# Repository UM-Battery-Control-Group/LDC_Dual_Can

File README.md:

# LDCquadCan
 can based LDC sensor

 Forgot to tie boot0 to ground so need to set nboot option in cube programmer

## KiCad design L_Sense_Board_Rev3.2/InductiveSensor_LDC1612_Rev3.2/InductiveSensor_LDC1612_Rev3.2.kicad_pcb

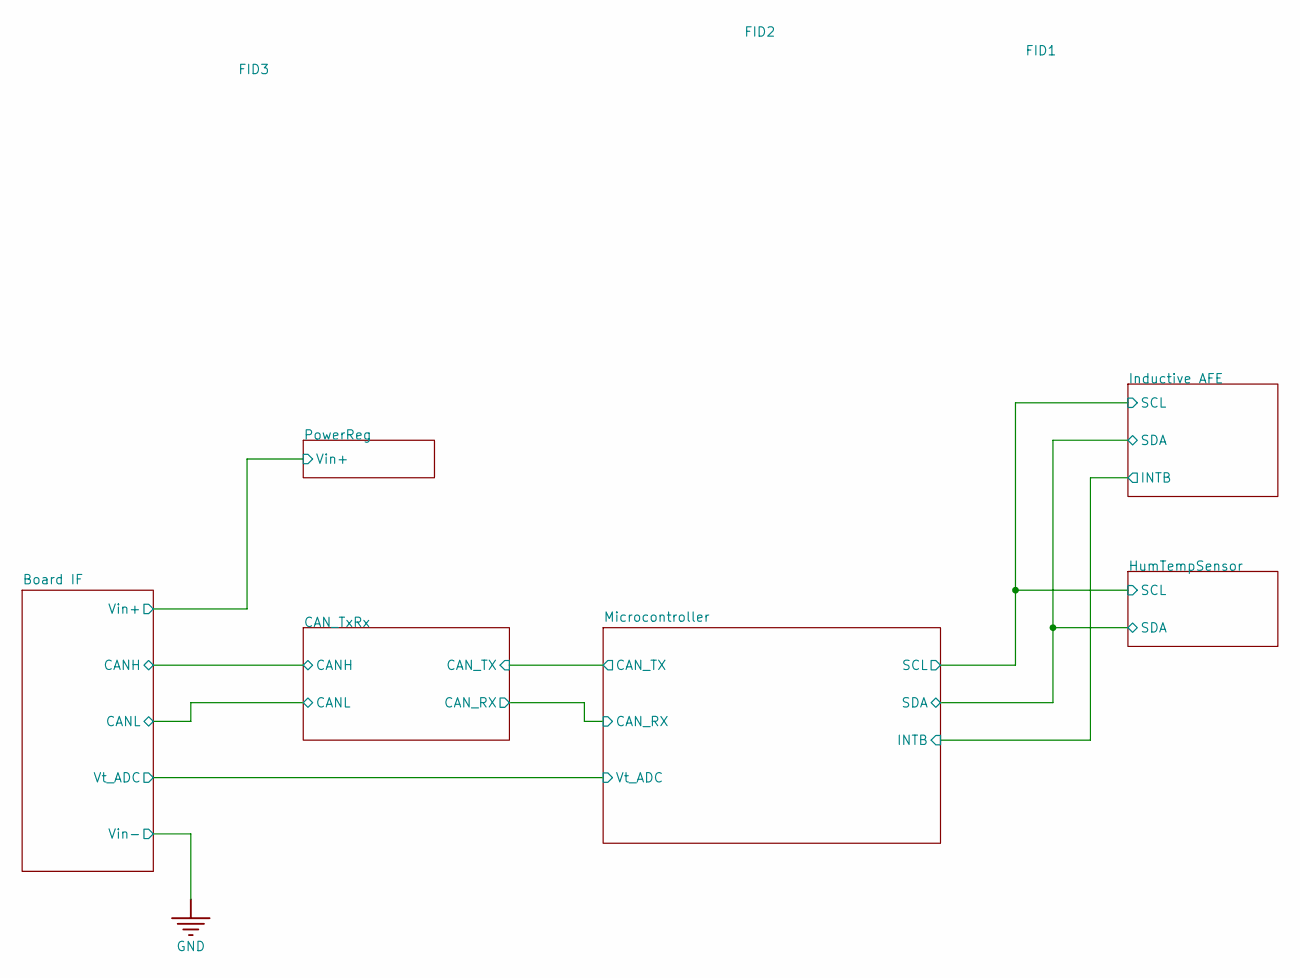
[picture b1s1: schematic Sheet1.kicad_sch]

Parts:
FID1, FID2, FID3: Fiducial; FID

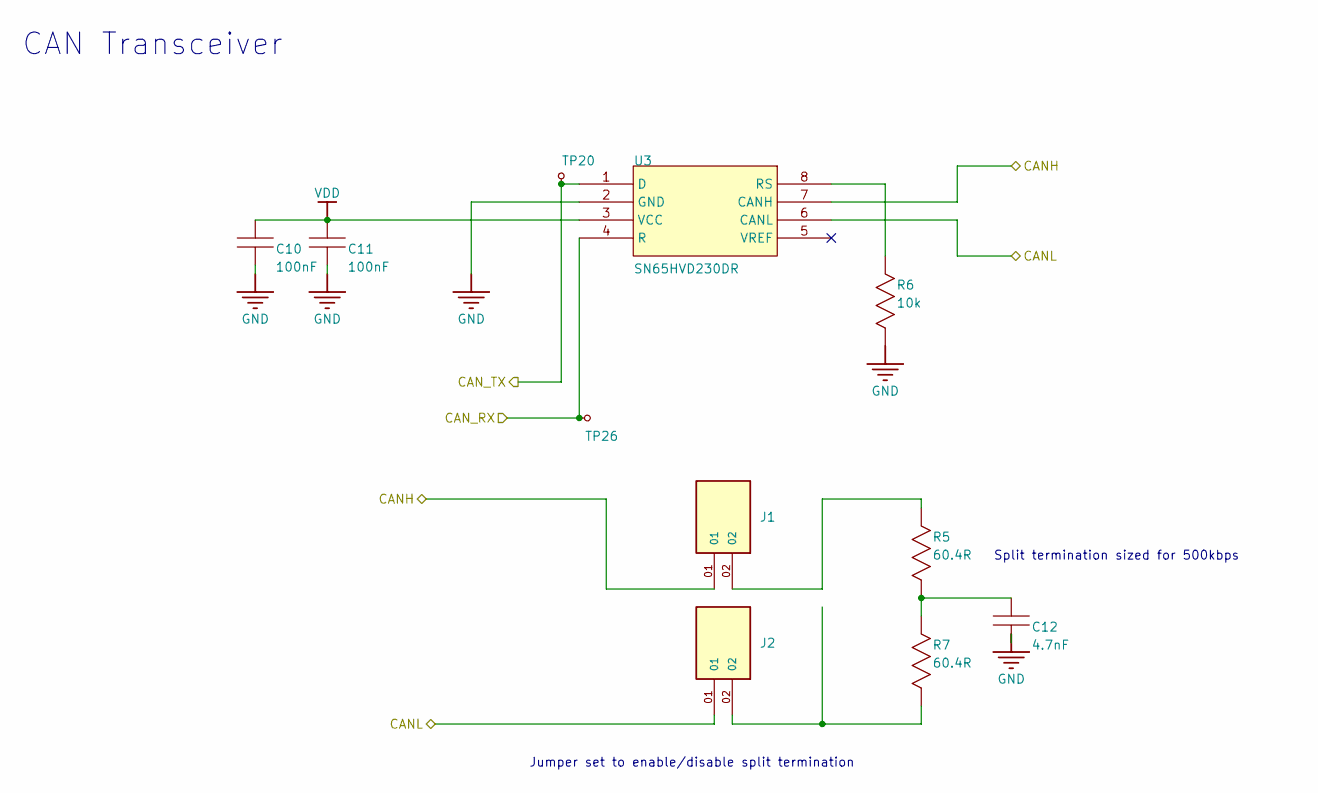
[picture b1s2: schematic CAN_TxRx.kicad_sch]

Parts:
C10, C11: 100nF; CAP0805; TOLERANCE 10%; VOLTAGE 50V; MANUFACTURER PART NUMBER CC0805KRX7R9BB104; LCSC PART# C49678
C12: 4.7nF; C0603; MANUFACTURER PART NUMBER C0603C472K1TACAUTO; LCSC PART# C3882427
J1, J2: TSM-102-01-X-SV; SAMTEC_TSM-102-01-X-SV; PARTREV D; DigiKey_Part_Number 612-TSM-102-01-S-SV-P-TRCT-ND
R5, R7: 60.4R; R0603; POWER RATING 100mW; TOLERANCE 1%; MANUFACTURER PART NUMBER RC0603FR-0760R4L; LCSC PART# C245987
R6: 10k; R0603; TOLERANCE 1%; VOLTAGE RATING (AC) 50V; MANUFACTURER PART NUMBER RC0603FR-0710KL; LCSC PART# C98220
TP20, TP26: 1mm Test Point; TP_1MM
U3: SN65HVD230DR; SOIC_8; MANUFACTURER PART NUMBER SN65HVD230DR; LCSC PART# C12084

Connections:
//Board IF/CANH: J1.01, U3.7 (CANH); also elsewhere on the board
//Board IF/CANL: J2.01, U3.6 (CANL); also elsewhere on the board
//CAN_TxRx/CAN_RX: TP26.1 (0), U3.4 (R); also elsewhere on the board
//CAN_TxRx/CAN_TX: TP20.1 (0), U3.1 (D); also elsewhere on the board
GND: C10.2, C11.2, C12.2, R6.2, U3.2 (GND); also elsewhere on the board
unnamed: C12.1, R5.2, R7.1
unnamed: J1.02, R5.1
unnamed: J2.02, R7.2
unnamed: R6.1, U3.8 (RS)
VDD: C10.1, C11.1, U3.3 (VCC); also elsewhere on the board

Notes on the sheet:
CAN Transceiver
Split termination sized for 500kbps
Jumper set to enable/disable split termination

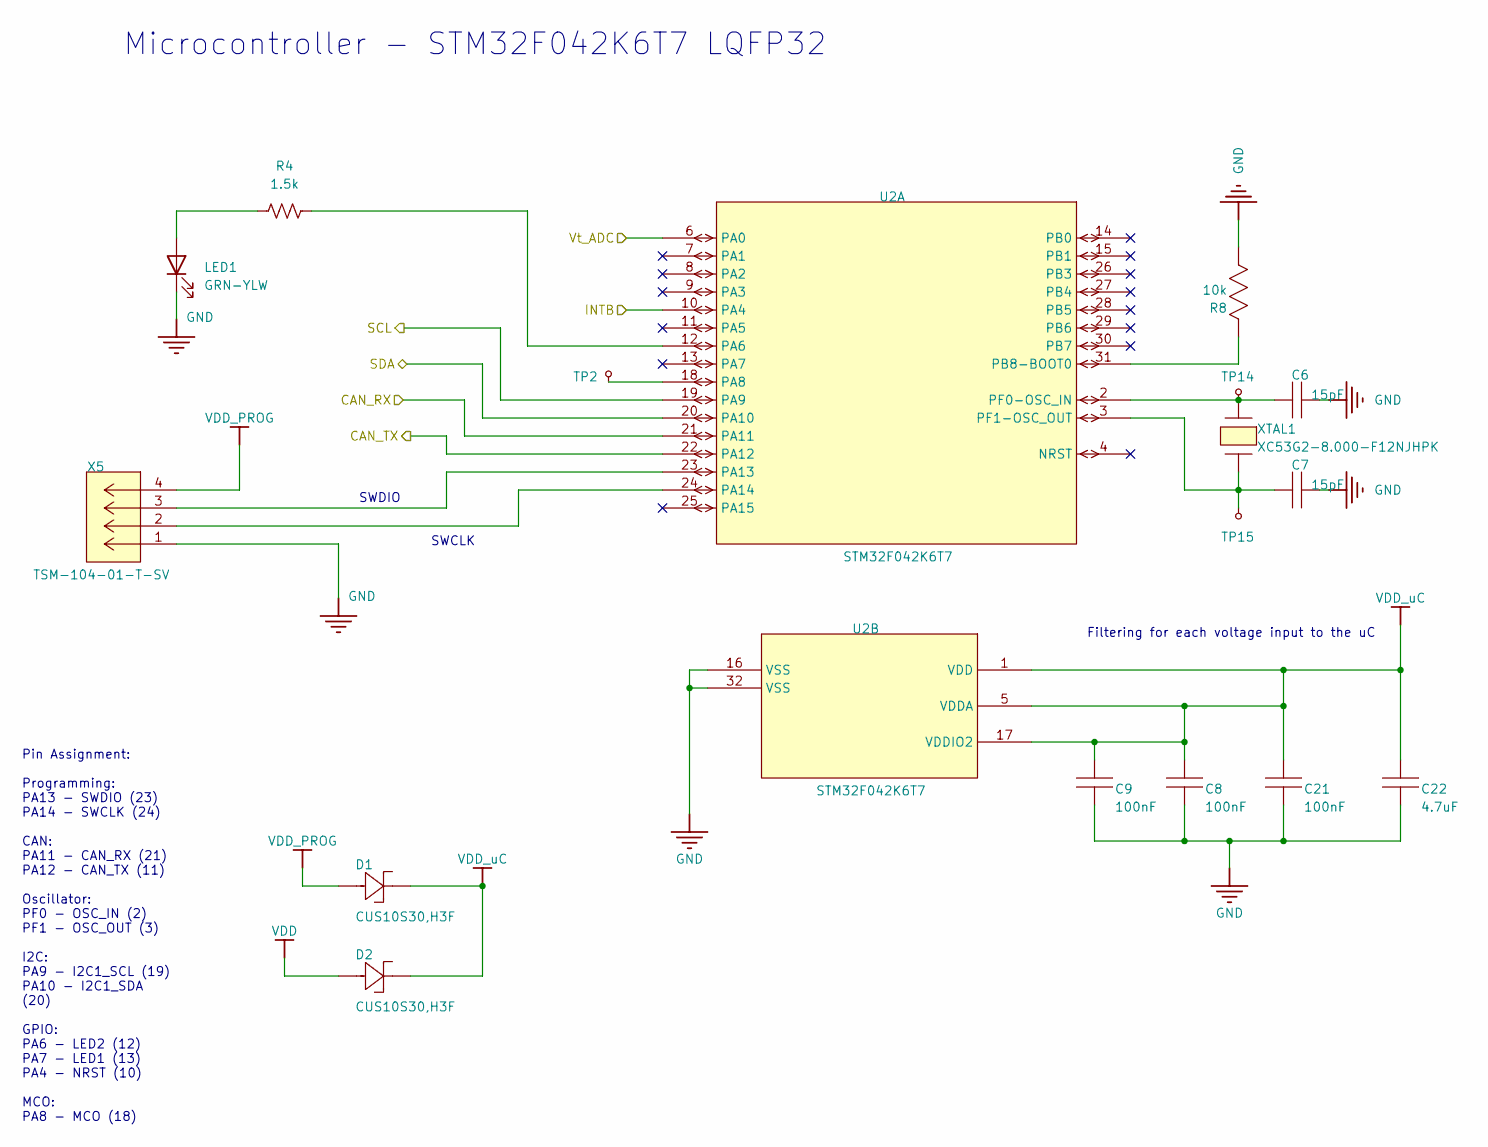
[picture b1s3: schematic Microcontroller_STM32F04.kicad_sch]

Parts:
C6, C7: 15pF; C0603; TOLERANCE 5%; VOLTAGE RATING 50V; MANUFACTURER PART NUMBER CL10C150JB81PNC
C8, C9, C21: 100nF; CAP0805; TOLERANCE 10%; VOLTAGE 50V; MANUFACTURER PART NUMBER CC0805KRX7R9BB104; LCSC PART# C49678
C22: 4.7uF; C_1206_3216Metric; TOLERANCE 10%; VOLTAGE 50V; MANUFACTURER PART NUMBER CC1206KFX7R9BB475
D1, D2: CUS10S30,H3F; USC_TOS; MANUFACTURER_PART_NUMBER CUS10S30,H3F; LCSC PART# C146335
LED1: GRN-YLW; LED_0603_1608Metric; MPN 5988E60107F
R4: 1.5k; R_0603_1608Metric; Part Number RC0603FR-7W1K5L
R8: 10k; R0603; TOLERANCE 1%; VOLTAGE RATING (AC) 50V; MANUFACTURER PART NUMBER RC0603FR-0710KL; LCSC PART# C98220
TP2, TP14, TP15: 1mm Test Point; TP_1MM
U2: STM32F042K6T7; LQFP-32; MANUFACTURER_PART_NUMBER STM32F042K6T7; LCSC PART# C1337340
X5: TSM-104-01-T-SV; CONN_TSM-104-01-T-SV_SAI; MAX VOLTAGE RATING (AC) 475V; FLAMMABILITY RATING UL94 V-0; MANUFACTURER_PART_NUMBER TSM-104-01-T-SV; LCSC PART# C3335977
XTAL1: XC53G2-8.000-F12NJHPK; XTAL_NX5032_NDK; MANUFACTURER_PART_NUMBER XC53G2-8.000-F12NJHPK; LCSC PART# C2842269

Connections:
//Board IF/Vt_ADC: U2.6 (PA0); also elsewhere on the board
//CAN_TxRx/CAN_RX: U2.21 (PA11); also elsewhere on the board
//CAN_TxRx/CAN_TX: U2.22 (PA12); also elsewhere on the board
//HumTempSensor/SCL: U2.19 (PA9); also elsewhere on the board
//HumTempSensor/SDA: U2.20 (PA10); also elsewhere on the board
//Inductive AFE/INTB: U2.10 (PA4); also elsewhere on the board
GND: C6.1, C7.1, C8.2, C9.2, C21.2, C22.2, LED1.1 (K), R8.2, U2.16 (VSS), U2.32 (VSS), X5.1; also elsewhere on the board
unnamed: LED1.2 (A), R4.1
unnamed: TP2.1 (0), U2.18 (PA8)
unnamed: C6.2, TP14.1 (0), U2.2 (PF0-OSC_IN), XTAL1.2
unnamed: C7.2, TP15.1 (0), U2.3 (PF1-OSC_OUT), XTAL1.1
unnamed: R4.2, U2.12 (PA6)
unnamed: U2.23 (PA13), X5.3
unnamed: U2.24 (PA14), X5.2
unnamed: R8.1, U2.31 (PB8-BOOT0)
VDD: D2.2 (anode); also elsewhere on the board
VDD_PROG: D1.2 (anode), X5.4
VDD_uC: C8.1, C9.1, C21.1, C22.1, D1.1 (cathode), D2.1 (cathode), U2.1 (VDD), U2.5 (VDDA), U2.17 (VDDIO2); also elsewhere on the board

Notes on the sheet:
SWDIO
Microcontroller - STM32F042K6T7 LQFP32
SWCLK
Filtering for each voltage input to the uC
Pin Assignment: Programming: PA13 - SWDIO (23) PA14 - SWCLK (24) CAN: PA11 - CAN_RX (21) PA12 - CAN_TX (11) Oscillator: PF0 - OSC_IN (2) PF1 - OSC_OUT (3) I2C: PA9 - I2C1_SCL (19) PA10 - I2C1_SDA (20) GPIO: PA6 - LED2 (12) PA7 - LED1 (13) PA4 - NRST (10) MCO: PA8 - MCO (18)

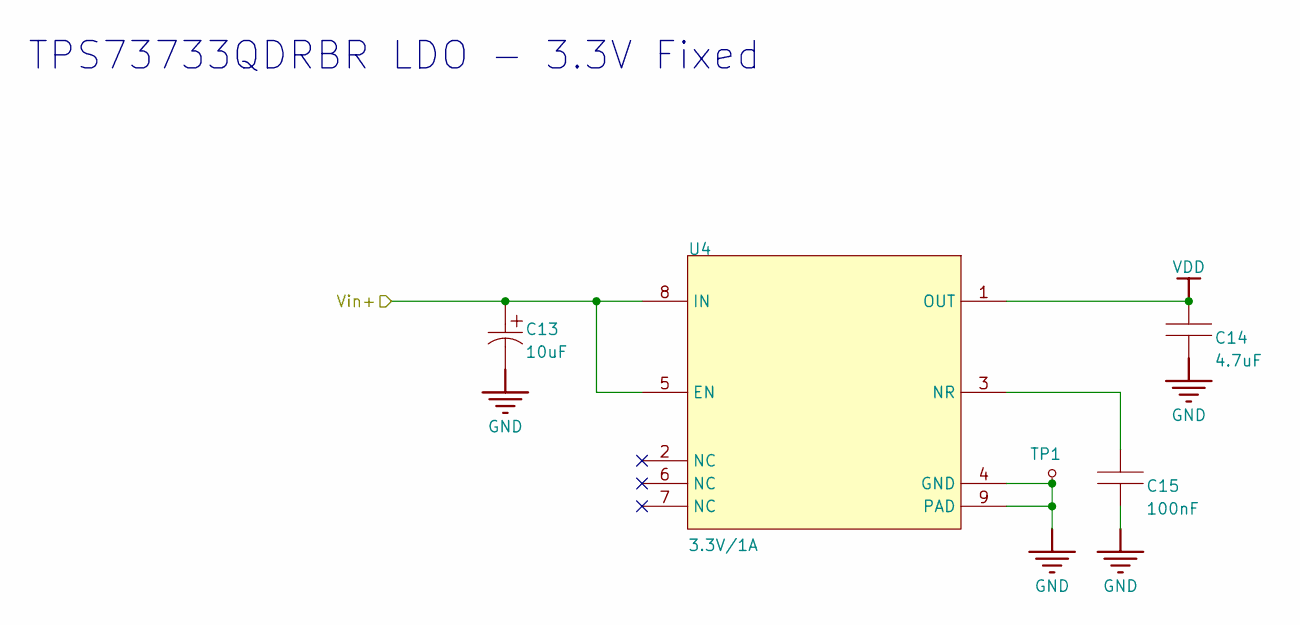
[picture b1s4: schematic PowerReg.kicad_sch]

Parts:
C13: 10uF; CAP1206_TAJA; TOLERANCE 10%; VOLTAGE RATING 16V; MANUFACTURER_PART_NUMBER TAJA106K016RNJ; LCSC PART# C7171
C14: 4.7uF; CAP0805; TOLERANCE 10%; VOLTAGE RATING 25V; MANUFACTURER PART NUMBER CL21A475KAQNNNE; LCSC PART# C1779
C15: 100nF; CAP0805; TOLERANCE 10%; VOLTAGE 50V; MANUFACTURER PART NUMBER CC0805KRX7R9BB104; LCSC PART# C49678
TP1: 1mm Test Point; TP_1MM
U4: 3.3V/1A; VSON_DRB8; OUTPUT VOLTAGE 3.3V; DROPOUT VOLTAGE 130mV; MANUFACTURER PART NUMBER TPS73733QDRBRQ1; LCSC PART# C523768

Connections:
//Board IF/Vin+: C13.1, U4.5 (EN), U4.8 (IN); also elsewhere on the board
GND: C13.2, C14.1, C15.2, TP1.1 (0), U4.4 (GND), U4.9 (PAD); also elsewhere on the board
unnamed: C15.1, U4.3 (NR)
VDD: C14.2, U4.1 (OUT); also elsewhere on the board

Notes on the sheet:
TPS73733QDRBR LDO - 3.3V Fixed

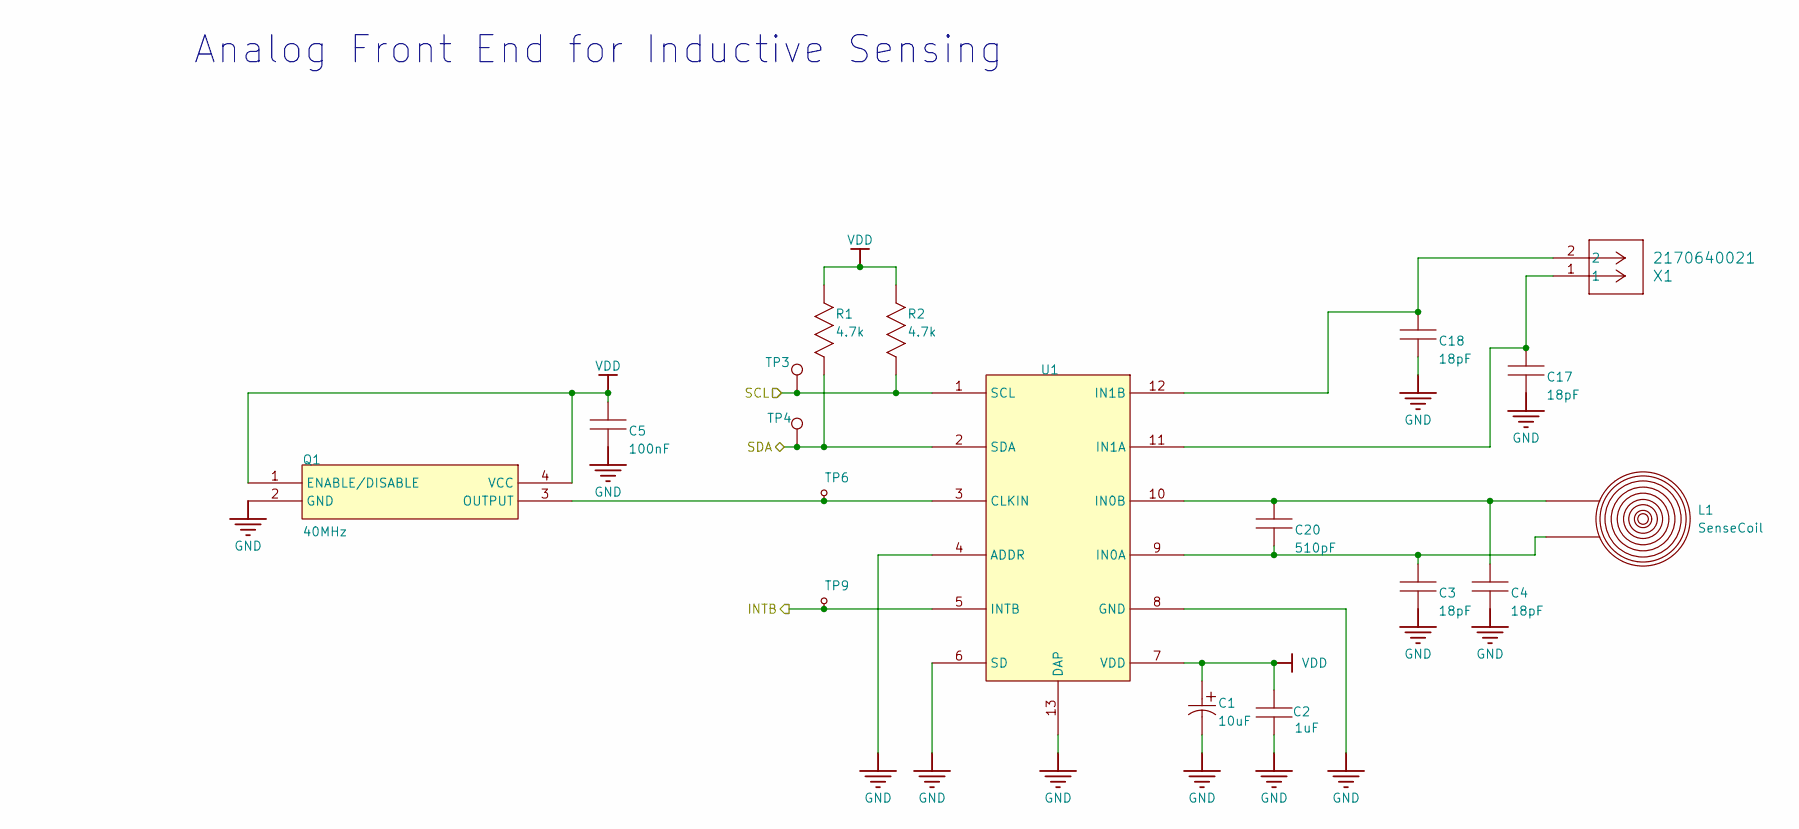
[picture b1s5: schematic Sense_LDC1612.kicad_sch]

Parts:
C1: 10uF; CAP1206_TAJA; TOLERANCE 10%; VOLTAGE RATING 16V; MANUFACTURER_PART_NUMBER TAJA106K016RNJ; LCSC PART# C7171
C2: 1uF; CAP0805; TOLERANCE 10%; VOLTAGE RATING 50V; MANUFACTURER PART NUMBER CL21B105KBFNNNE; LCSC PART# C28323
C3, C4, C17, C18: 18pF; CAP0805; TOLERANCE 5%; VOLTAGE RATING 50V; MANUFACTURER PART NUMBER VJ0805A180JXACW1BC; LCSC PART# C2174299
C5: 100nF; CAP0805; TOLERANCE 10%; VOLTAGE 50V; MANUFACTURER PART NUMBER CC0805KRX7R9BB104; LCSC PART# C49678
C20: 510pF; CAP0805; TOLERANCE 5%; VOLTAGE RATING (DC) 50V; MANUFACTURER PART NUMBER CC0805JRNPO9BN511; LCSC PART# C309486
L1: SenseCoil; COIL_4L
Q1: 40MHz; KC2520Z_KYO; MANUFACTURER PART NUMBER KC2520Z40.0000C15XXK; LCSC PART# C1857241
R1, R2: 4.7k; RES0805; TOLERANCE 5%; POWER RATING 125mW; MANUFACTURER PART NUMBER ERJ-6GEYJ472V; LCSC PART# C230645
TP3, TP4: TestPoint; TP_1MM
TP6, TP9: 1mm Test Point; TP_1MM
U1: Inductive Sensor 2Ch; LDC1612; MANUFACTURER PART NUMBER LDC1612DNTR; LCSC PART# C1847959
X1: 2170640021; CONN_2170630000-SD_02_MOL; MANUFACTURER PART NUMBER 2170640021

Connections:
//HumTempSensor/SCL: R2.2, TP3.1, U1.1 (SCL); also elsewhere on the board
//HumTempSensor/SDA: R1.2, TP4.1, U1.2 (SDA); also elsewhere on the board
//Inductive AFE/INTB: TP9.1 (0), U1.5 (INTB); also elsewhere on the board
GND: C1.2, C2.2, C3.2, C4.2, C5.2, C17.2, C18.2, Q1.2 (GND), U1.4 (ADDR), U1.6 (SD), U1.8 (GND), U1.13 (DAP); also elsewhere on the board
unnamed: Q1.3 (OUTPUT), TP6.1 (0), U1.3 (CLKIN)
unnamed: C3.1, C20.1, L1.1, U1.9 (IN0A)
unnamed: C4.1, C20.2, L1.2, U1.10 (IN0B)
unnamed: C17.1, U1.11 (IN1A), X1.1
unnamed: C18.1, U1.12 (IN1B), X1.2
VDD: C1.1, C2.1, C5.1, Q1.1 (ENABLE/DISABLE), Q1.4 (VCC), R1.1, R2.1, U1.7 (VDD); also elsewhere on the board

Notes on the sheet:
Analog Front End for Inductive Sensing

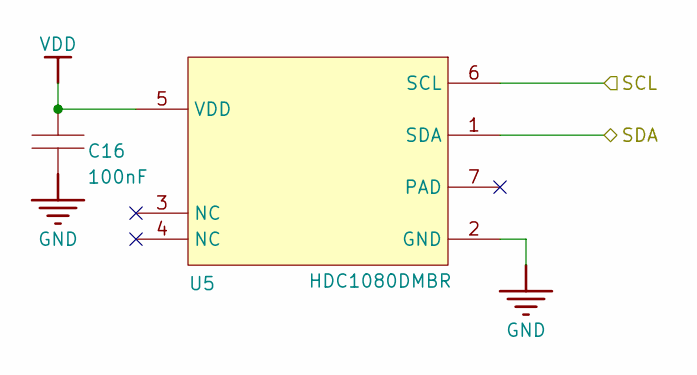
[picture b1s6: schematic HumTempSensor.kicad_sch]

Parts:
C16: 100nF; CAP0805; TOLERANCE 10%; VOLTAGE 50V; MANUFACTURER PART NUMBER CC0805KRX7R9BB104; LCSC PART# C49678
U5: I2C Humidity/Temp Sensor; WSON_DMB6; MANUFACTURER PART NUMBER HDC1080DMBR; LCSC PART# C82227

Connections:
//HumTempSensor/SCL: U5.6 (SCL); also elsewhere on the board
//HumTempSensor/SDA: U5.1 (SDA); also elsewhere on the board
GND: C16.2, U5.2 (GND); also elsewhere on the board
VDD: C16.1, U5.5 (VDD); also elsewhere on the board

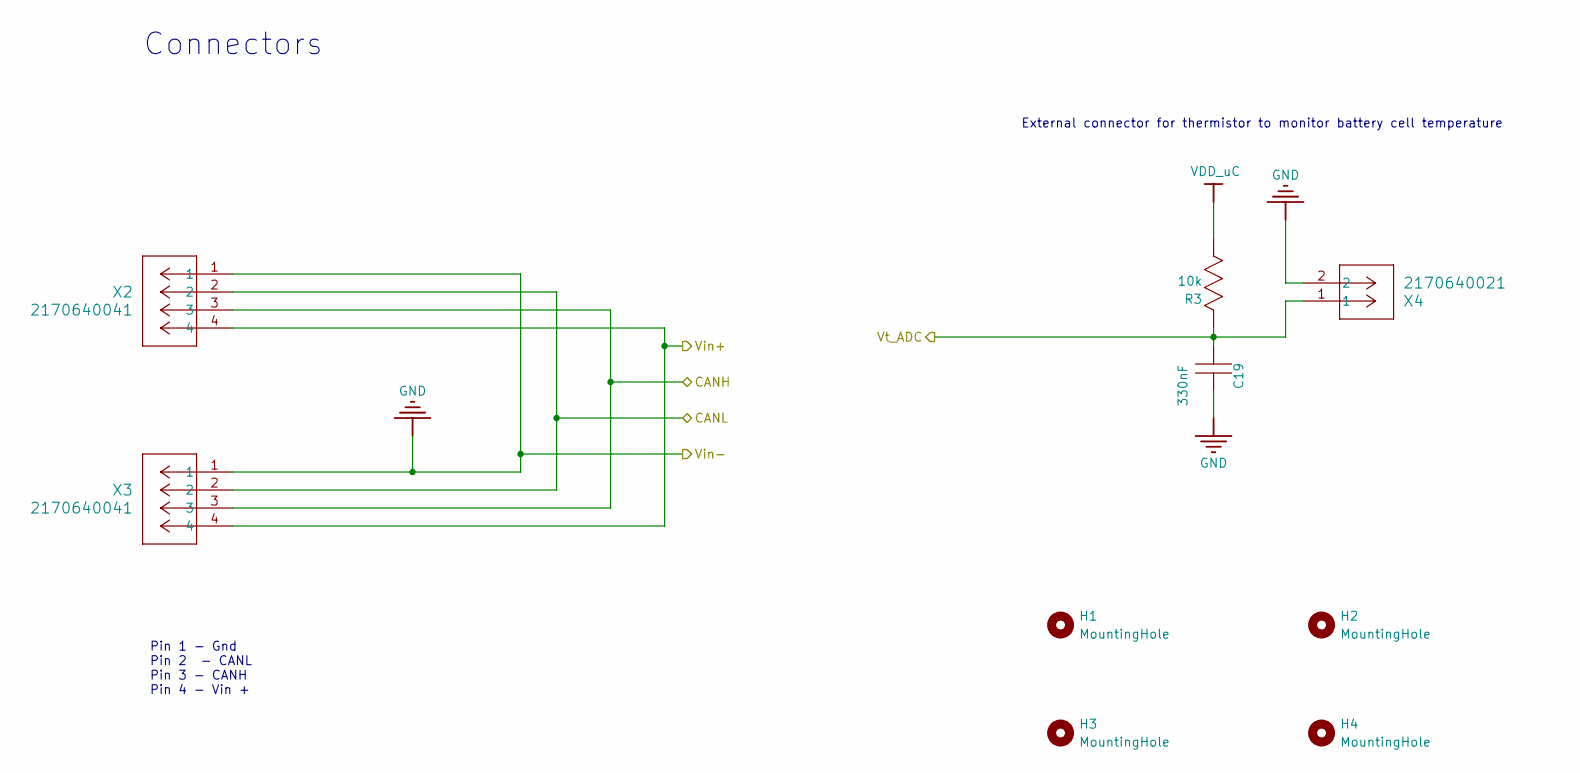
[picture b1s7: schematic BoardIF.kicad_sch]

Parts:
C19: 330nF; C0603; VOLTAGE RATING 50V; VOLTAGE 50V; MANUFACTURER PART NUMBER 0603B334K500XD
H1, H2, H3, H4: MountingHole; MountingHole_3.2mm_M3
R3: 10k; R0603; TOLERANCE 1%; VOLTAGE RATING (AC) 50V; MANUFACTURER PART NUMBER RC0603FR-0710KL; LCSC PART# C98220
X2, X3: 2170640041; CONN_2170630000-SD_04_MOL; MANUFACTURER PART NUMBER 2170640041
X4: 2170640021; CONN_2170630000-SD_02_MOL; MANUFACTURER PART NUMBER 2170640021

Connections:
//Board IF/CANH: X2.3, X3.3; also elsewhere on the board
//Board IF/CANL: X2.2, X3.2; also elsewhere on the board
//Board IF/Vin+: X2.4, X3.4; also elsewhere on the board
//Board IF/Vt_ADC: C19.2, R3.1, X4.1; also elsewhere on the board
GND: C19.1, X2.1, X3.1, X4.2; also elsewhere on the board
VDD_uC: R3.2; also elsewhere on the board

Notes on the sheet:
External connector for thermistor to monitor battery cell temperature
Connectors
Pin 1 - Gnd Pin 2 - CANL Pin 3 - CANH Pin 4 - Vin +

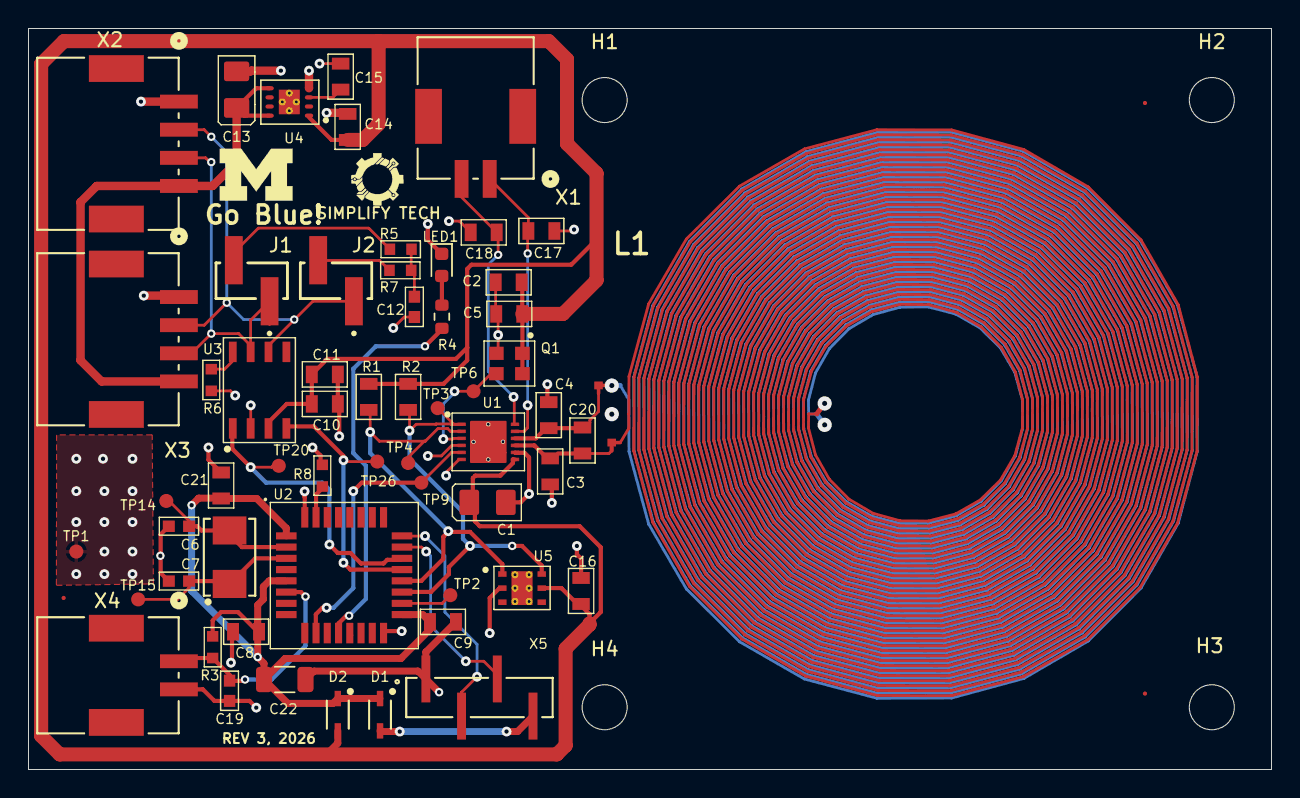
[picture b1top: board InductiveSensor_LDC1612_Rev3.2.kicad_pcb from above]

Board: 4 copper layers, 88.4 x 52.7 mm, 65 parts (0 on the bottom side), 31 nets.

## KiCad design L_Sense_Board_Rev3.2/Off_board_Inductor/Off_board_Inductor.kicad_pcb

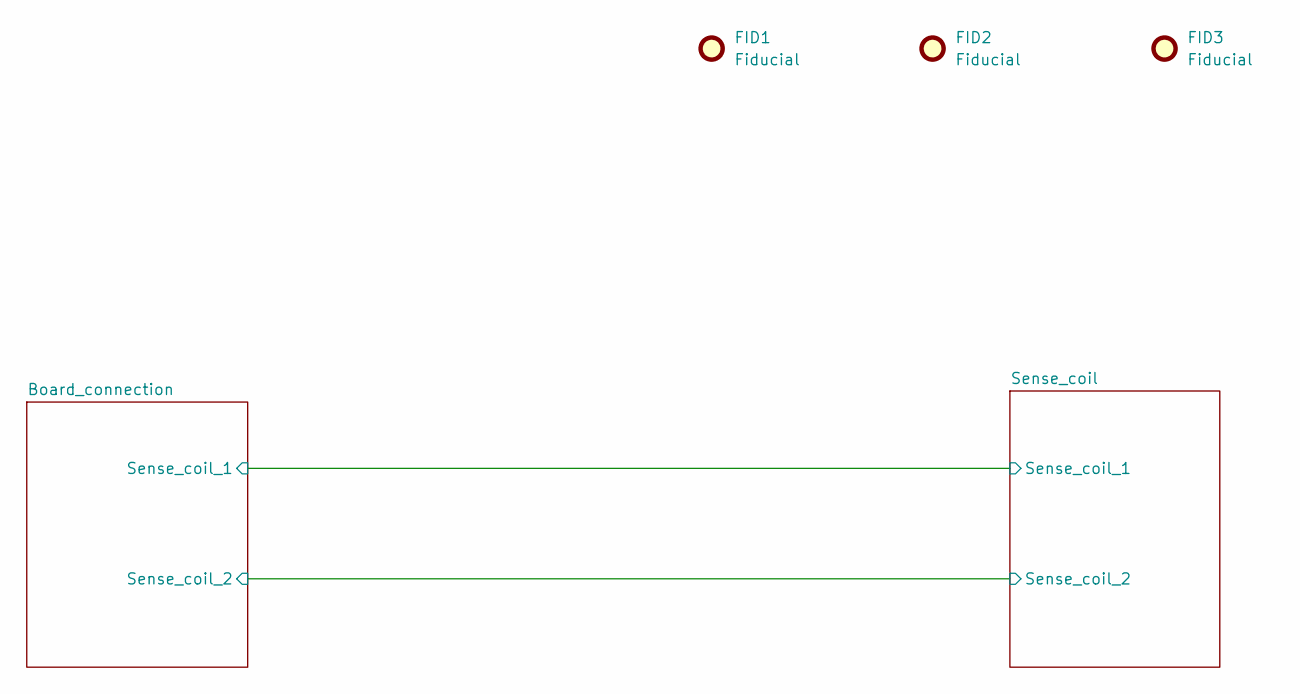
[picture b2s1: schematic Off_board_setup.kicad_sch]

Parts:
FID1, FID2, FID3: Fiducial; FID

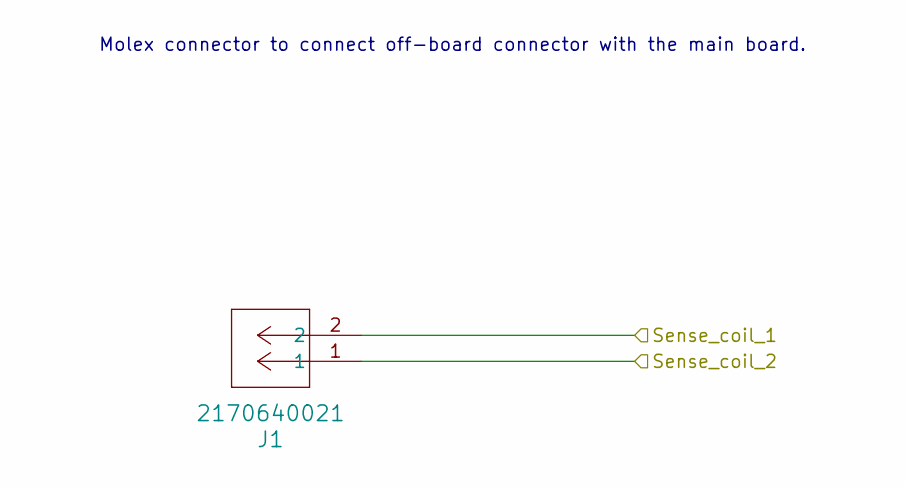
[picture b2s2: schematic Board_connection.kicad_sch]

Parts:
J1: 2170640021; CONN_2170630000-SD_02_MOL

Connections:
/Off_board_inductor/Board_connection/Sense_coil_1: J1.2; also elsewhere on the board
/Off_board_inductor/Board_connection/Sense_coil_2: J1.1; also elsewhere on the board

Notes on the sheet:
Molex connector to connect off-board connector with the main board.

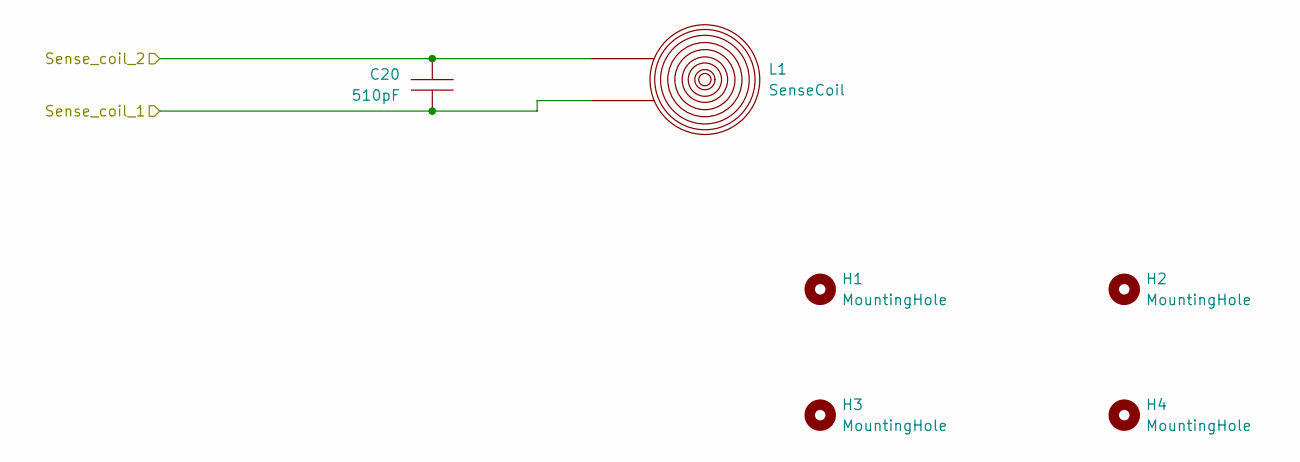
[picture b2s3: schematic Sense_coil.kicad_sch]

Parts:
C20: 510pF; CAP0805; TOLERANCE 5%; VOLTAGE RATING (DC) 50V; MANUFACTURER PART NUMBER CC0805JRNPO9BN511
H1, H2, H3, H4: MountingHole; MountingHole_3.2mm_M3
L1: SenseCoil; COIL_4L

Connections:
/Off_board_inductor/Board_connection/Sense_coil_1: C20.1, L1.1; also elsewhere on the board
/Off_board_inductor/Board_connection/Sense_coil_2: C20.2, L1.2; also elsewhere on the board

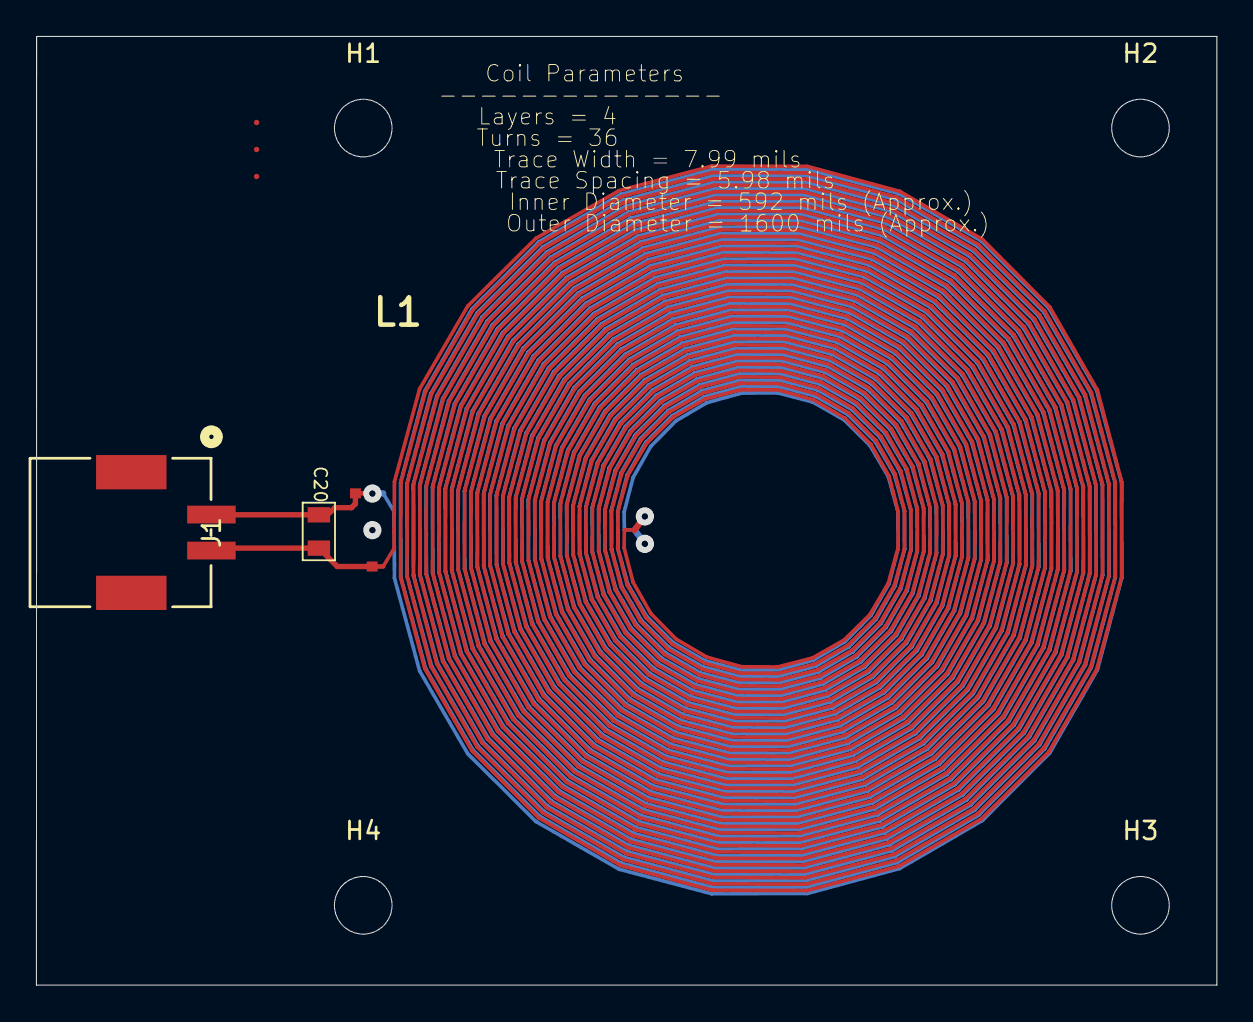
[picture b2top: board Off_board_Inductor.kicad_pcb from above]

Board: 4 copper layers, 65.6 x 52.7 mm, 10 parts (0 on the bottom side), 2 nets.

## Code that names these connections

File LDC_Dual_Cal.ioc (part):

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Mcu.Name=STM32F042K(4-6)Tx
Mcu.Package=LQFP32
Mcu.UserName=STM32F042K6Tx
PA0.Mode=IN0
PA0.Signal=ADC_IN0
PA10.Mode=I2C
PA10.Signal=I2C1_SDA
PA11.Mode=CAN_Activate
PA11.Signal=CAN_RX
PA12.Mode=CAN_Activate
PA12.Signal=CAN_TX
PA13.Mode=Serial_Wire
PA13.Signal=SYS_SWDIO
PA14.Mode=Serial_Wire
PA14.Signal=SYS_SWCLK
PA4.GPIOParameters=GPIO_ModeDefaultEXTI
PA4.GPIO_ModeDefaultEXTI=GPIO_MODE_IT_FALLING
PA4.Signal=GPXTI4
PA6.Signal=GPIO_Output
PA7.Signal=GPIO_Output
PA9.Mode=I2C
PA9.Signal=I2C1_SCL
PF0-OSC_IN.Mode=HSE-External-Oscillator
PF0-OSC_IN.Signal=RCC_OSC_IN
PF1-OSC_OUT.Mode=HSE-External-Oscillator
PF1-OSC_OUT.Signal=RCC_OSC_OUT
RCC.SYSCLKFreq_VALUE=16000000
RCC.SYSCLKSource=RCC_SYSCLKSOURCE_PLLCLK
board=custom

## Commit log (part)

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2024-01-08 fist pass
    can blink an LED>
2024-01-26 tested working code for new Dual channel boards
    Need to check LDC configuration, and timing. but tested and seems to work,
    Using timer channel 3 for interrupt based sampling of the board.
2024-02-05 code and setting update
2024-02-12 updated code with can interrupts enabled
2024-02-14 removed space hogs
2024-02-14 more changes to local files
    agh
2024-02-14 remove asc logging
    removed asc logs
2024-02-15 fix sampling rate and N=50 samples
    fix sampling rate issue and N=50, potential overflow bug.
2026-05-11 Remove V1 board hardware and Add Ver 3.2 board hardware
    Remove V1 board hardware and Add Ver 3.2 board hardware
2026-05-13 change can bitrate to 125
    changed the can bitrate to 125k
2026-06-03 Add thermistor reading support in firmware and logger
2026-06-09 Set ADC sampling time to max (239.5 cyc)

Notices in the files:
parts and their libraries:
COPYRIGHT: Copyright (C) 2023 Ultra Librarian. All rights reserved.
